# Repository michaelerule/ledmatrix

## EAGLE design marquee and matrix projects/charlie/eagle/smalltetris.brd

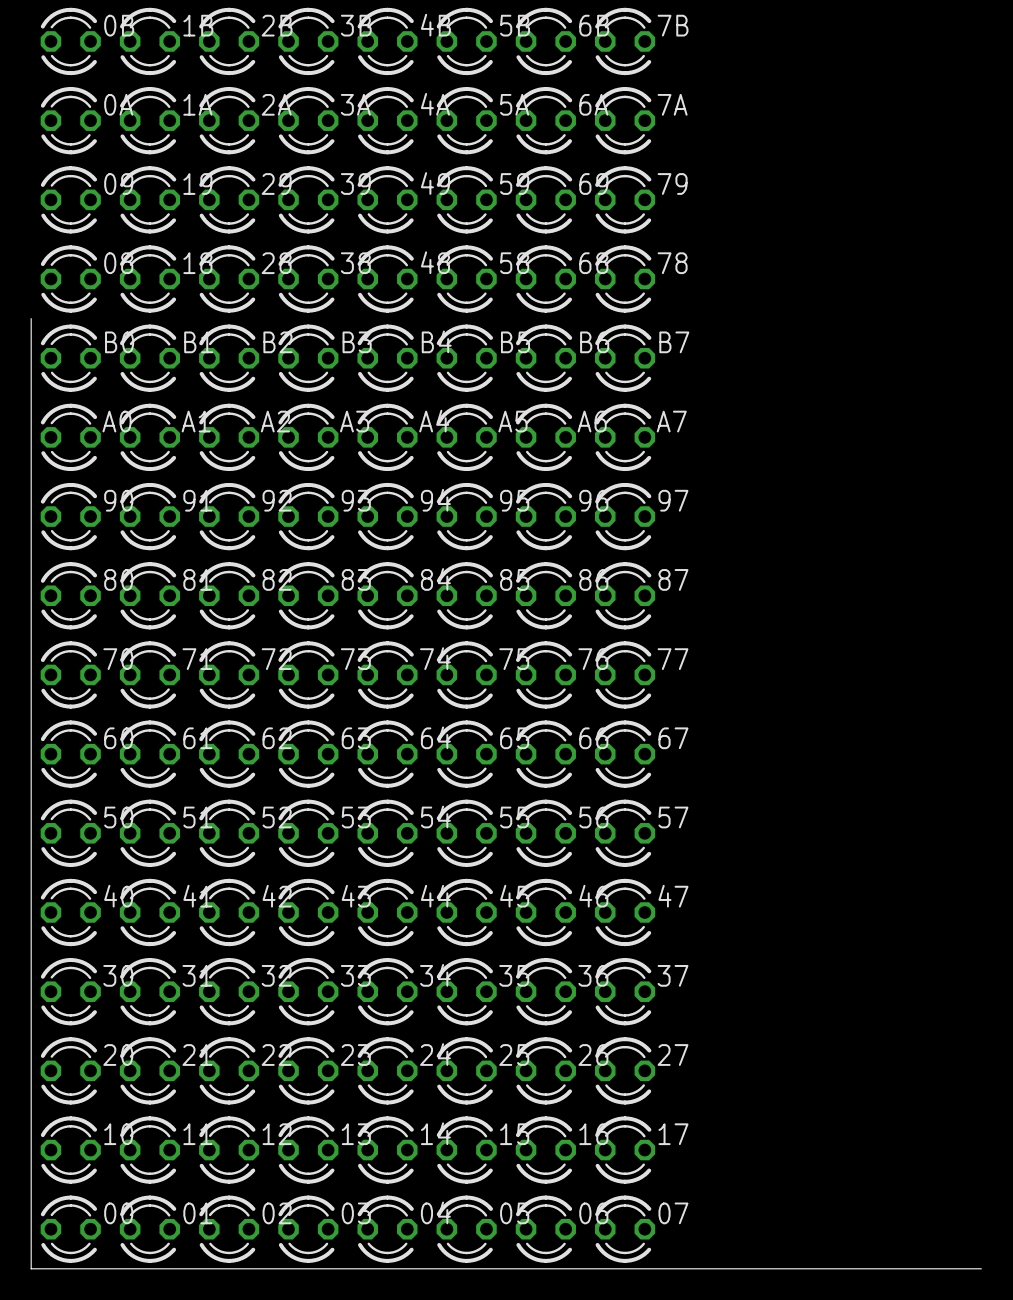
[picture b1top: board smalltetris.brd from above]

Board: 2 copper layers, 128 parts (0 on the bottom side), 13 nets, no tracks yet.

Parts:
00, 0A, 0B, 01, 1A, 1B, 02, 2A, 2B, 03, 3A, 3B, 04, 4A, 4B, 05, 5A, 5B, 06, 6A, 6B, 07, 7A, 7B, 08, 09, 10, 11, 12, 13, 14, 15, 16, 17, 18, 19, 20, 21, 22, 23, 24, 25, 26, 27, 28, 29, 30, 31, 32, 33, 34, 35, 36, 37, 38, 39, 40, 41, 42, 43, 44, 45, 46, 47, 48, 49, 50, 51, 52, 53, 54, 55, 56, 57, 58, 59, 60, 61, 62, 63, 64, 65, 66, 67, 68, 69, 70, 71, 72, 73, 74, 75, 76, 77, 78, 79, 80, 81, 82, 83, 84, 85, 86, 87, 90, 91, 92, 93, 94, 95, 96, 97: LED3MM
A0, A1, A2, A3, A4, A5, A6, A7: LED3MM
B0, B1, B2, B3, B4, B5, B6, B7: LED3MM

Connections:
D: 00.A, 11.A, 22.A, 33.A, 44.A, 55.A, 66.A, 77.A
S0: 00.K, 0A.A, 0B.A, 01.A, 02.A, 03.A, 04.A, 05.A, 06.A, 07.A, 08.A, 09.A, 10.K, 20.K, 30.K, 40.K, 50.K, 60.K, 70.K, 80.K, 90.K, A0.K, B0.K
S1: 01.K, 1A.A, 1B.A, 10.A, 11.K, 12.A, 13.A, 14.A, 15.A, 16.A, 17.A, 18.A, 19.A, 21.K, 31.K, 41.K, 51.K, 61.K, 71.K, 81.K, 91.K, A1.K, B1.K
S2: 02.K, 2A.A, 2B.A, 12.K, 20.A, 21.A, 22.K, 23.A, 24.A, 25.A, 26.A, 27.A, 28.A, 29.A, 32.K, 42.K, 52.K, 62.K, 72.K, 82.K, 92.K, A2.K, B2.K
S3: 03.K, 3A.A, 3B.A, 13.K, 23.K, 30.A, 31.A, 32.A, 33.K, 34.A, 35.A, 36.A, 37.A, 38.A, 39.A, 43.K, 53.K, 63.K, 73.K, 83.K, 93.K, A3.K, B3.K
S4: 04.K, 4A.A, 4B.A, 14.K, 24.K, 34.K, 40.A, 41.A, 42.A, 43.A, 44.K, 45.A, 46.A, 47.A, 48.A, 49.A, 54.K, 64.K, 74.K, 84.K, 94.K, A4.K, B4.K
S5: 05.K, 5A.A, 5B.A, 15.K, 25.K, 35.K, 45.K, 50.A, 51.A, 52.A, 53.A, 54.A, 55.K, 56.A, 57.A, 58.A, 59.A, 65.K, 75.K, 85.K, 95.K, A5.K, B5.K
S6: 06.K, 6A.A, 6B.A, 16.K, 26.K, 36.K, 46.K, 56.K, 60.A, 61.A, 62.A, 63.A, 64.A, 65.A, 66.K, 67.A, 68.A, 69.A, 76.K, 86.K, 96.K, A6.K, B6.K
S7: 07.K, 7A.A, 7B.A, 17.K, 27.K, 37.K, 47.K, 57.K, 67.K, 70.A, 71.A, 72.A, 73.A, 74.A, 75.A, 76.A, 77.K, 78.A, 79.A, 87.K, 97.K, A7.K, B7.K
S8: 08.K, 18.K, 28.K, 38.K, 48.K, 58.K, 68.K, 78.K, 80.A, 81.A, 82.A, 83.A, 84.A, 85.A, 86.A, 87.A
S9: 09.K, 19.K, 29.K, 39.K, 49.K, 59.K, 69.K, 79.K, 90.A, 91.A, 92.A, 93.A, 94.A, 95.A, 96.A, 97.A
S10: 0A.K, 1A.K, 2A.K, 3A.K, 4A.K, 5A.K, 6A.K, 7A.K, A0.A, A1.A, A2.A, A3.A, A4.A, A5.A, A6.A, A7.A
S11: 0B.K, 1B.K, 2B.K, 3B.K, 4B.K, 5B.K, 6B.K, 7B.K, B0.A, B1.A, B2.A, B3.A, B4.A, B5.A, B6.A, B7.A

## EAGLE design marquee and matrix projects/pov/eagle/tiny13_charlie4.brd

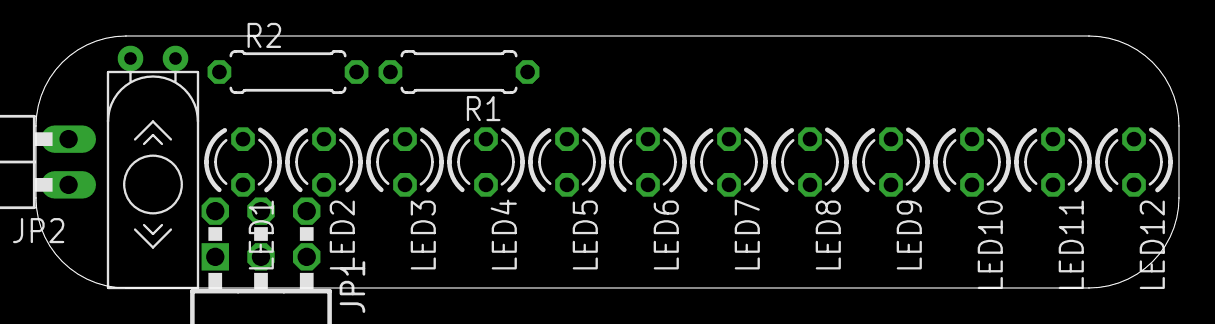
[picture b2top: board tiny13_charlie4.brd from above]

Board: 2 copper layers, 63.5 x 14.0 mm, 18 parts (1 on the bottom side), 8 nets, no tracks yet.

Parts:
IC1: TINY13-20SSU; 8S1
JP1: AVR-ISP-6R
JP2: 1X02/90
LED1, LED2, LED3, LED4, LED5, LED6, LED7, LED8, LED9, LED10, LED11, LED12: LED3MM
R1, R2: 0207/7
U$1: TILT_SWITCH_MECHANICAL

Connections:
GND: IC1.1, IC1.4, JP1.5, JP1.6, JP2.2, R1.2, R2.1
unnamed: IC1.2, LED3.K, LED4.A, LED5.K, LED6.A, LED7.A, LED8.K
unnamed: IC1.7, JP1.3, LED1.K, LED2.A, LED3.A, LED4.K, LED11.A, LED12.K
unnamed: R2.2, U$1.P$2
unnamed: IC1.3, LED7.K, LED8.A, LED9.K, LED10.A, LED11.K, LED12.A
unnamed: IC1.5, JP1.4, U$1.P$1
unnamed: IC1.6, JP1.1, LED1.A, LED2.K, LED5.A, LED6.K, LED9.A, LED10.K
VCC: IC1.8, JP1.2, JP2.1, R1.1

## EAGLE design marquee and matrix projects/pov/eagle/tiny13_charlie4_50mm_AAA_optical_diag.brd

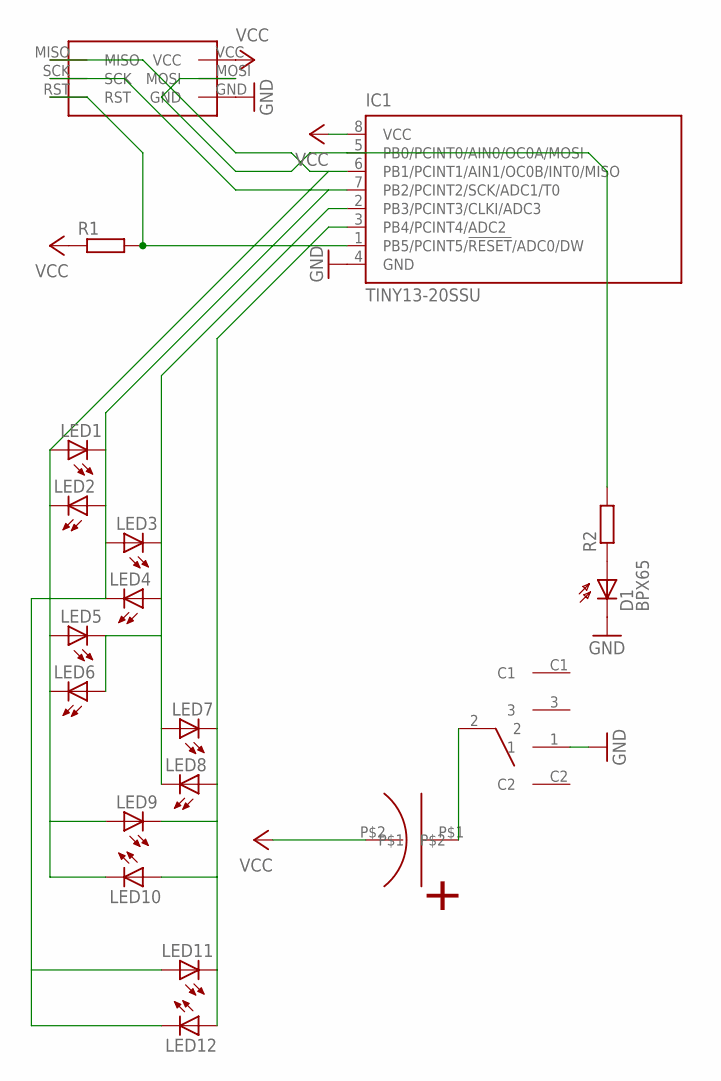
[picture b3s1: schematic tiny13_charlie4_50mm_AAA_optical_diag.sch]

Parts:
D1: BPX65
IC1: TINY13-20SSU; 8S1
LED1, LED2, LED3, LED4, LED5, LED6, LED7, LED8, LED9, LED10, LED11, LED12: LED3MM
R1, R2: R-EU_0204/5; 0204/5
U$2: AVR_ISP_6_PIN_1X6_SMT_CONTACT_BIG; CONTACT_ISP_PROGRAMMER_1X6_ATMEL
U$4: SWITCH
U$5: NICHICON_12F; NICHICON_10X30

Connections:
GND: D1.K (C), IC1.4 (GND), U$2.GND, U$4.1
unnamed: IC1.2 (PB3/PCINT3/CLKI/ADC3), LED3.K (C), LED4.A, LED5.K (C), LED6.A, LED7.A, LED8.K (C)
unnamed: IC1.7 (PB2/PCINT2/SCK/ADC1/T0), LED1.K (C), LED2.A, LED3.A, LED4.K (C), LED11.A, LED12.K (C), U$2.SCK
unnamed: D1.A, R2.1
unnamed: IC1.3 (PB4/PCINT4/ADC2), LED7.K (C), LED8.A, LED9.K (C), LED10.A, LED11.K (C), LED12.A
unnamed: IC1.5 (PB0/PCINT0/AIN0/OC0A/MOSI), R2.2, U$2.MOSI
unnamed: IC1.1 (PB5/PCINT5/!RESET!/ADC0/DW), R1.2, U$2.RST
unnamed: U$4.2, U$5.P$1
unnamed: IC1.6 (PB1/PCINT1/AIN1/OC0B/INT0/MISO), LED1.A, LED2.K (C), LED5.A, LED6.K (C), LED9.A, LED10.K (C), U$2.MISO
VCC: IC1.8 (VCC), R1.1, U$2.VCC, U$5.P$2

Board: 2 copper layers, 19 parts (2 on the bottom side), 10 nets, no tracks yet.

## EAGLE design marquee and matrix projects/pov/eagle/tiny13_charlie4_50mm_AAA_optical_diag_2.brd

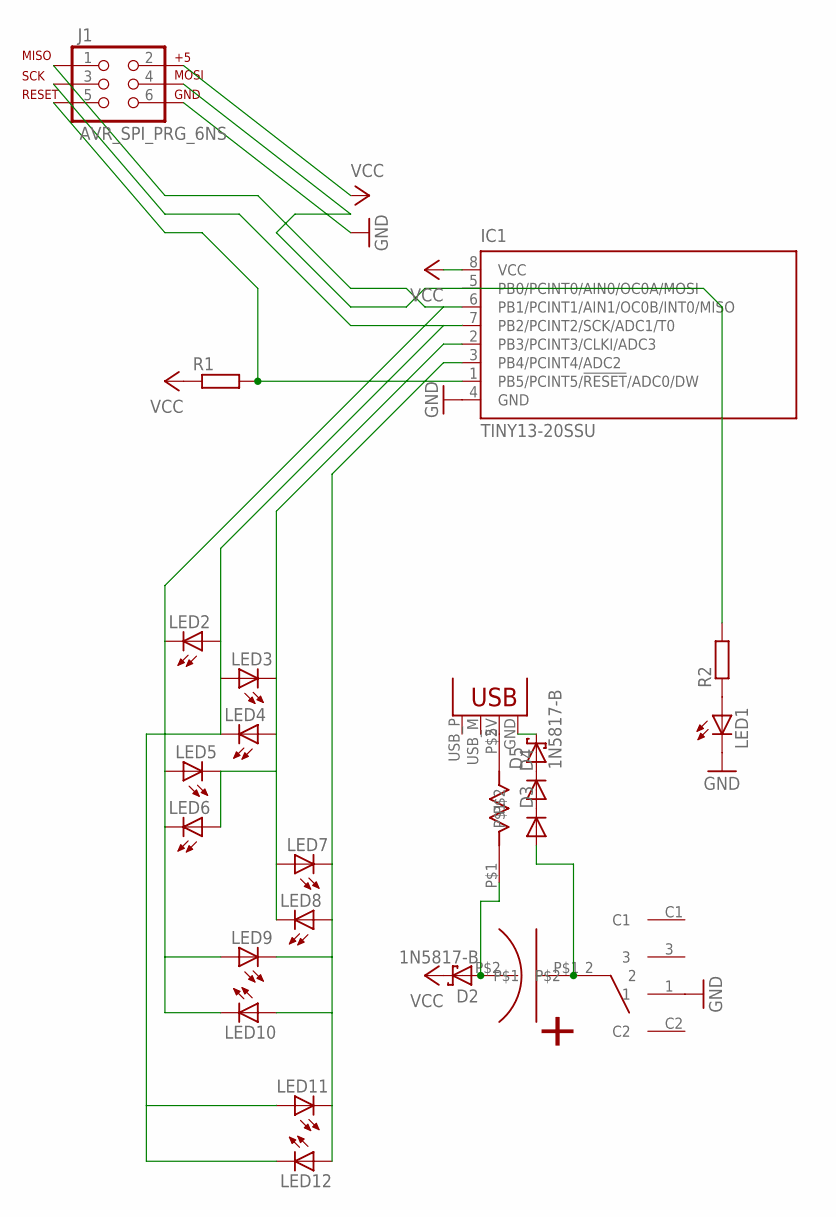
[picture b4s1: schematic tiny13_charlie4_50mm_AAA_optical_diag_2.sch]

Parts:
D2, D5: 1N5817-B; DO41-7.6
D3, D4: DIODE-D-5; D-5
IC1: TINY13-20SSU; 8S1
J1: AVR_SPI_PRG_6NS; 2X3-NS
LED1, LED2, LED3, LED4, LED5, LED6, LED7, LED8, LED9, LED10, LED11, LED12: LED3MM
R1, R2: R-EU_0204/5; 0204/5
U$1: R-7
U$4: SWITCH
U$5: NICHICON_12F; NICHICON_10X30
X1: USBPCB; USB-A-PCB

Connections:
GND: IC1.4 (GND), J1.6, LED1.K (C), U$4.1
unnamed: IC1.2 (PB3/PCINT3/CLKI/ADC3), LED3.K (C), LED4.A, LED5.K (C), LED6.A, LED7.A, LED8.K (C)
unnamed: IC1.7 (PB2/PCINT2/SCK/ADC1/T0), J1.3, LED2.A, LED3.A, LED4.K (C), LED11.A, LED12.K (C)
unnamed: LED1.A, R2.1
unnamed: IC1.3 (PB4/PCINT4/ADC2), LED7.K (C), LED8.A, LED9.K (C), LED10.A, LED11.K (C), LED12.A
unnamed: IC1.5 (PB0/PCINT0/AIN0/OC0A/MOSI), J1.4, R2.2
unnamed: IC1.1 (PB5/PCINT5/!RESET!/ADC0/DW), J1.5, R1.2
unnamed: D3.A, U$4.2, U$5.P$1
unnamed: IC1.6 (PB1/PCINT1/AIN1/OC0B/INT0/MISO), J1.1, LED2.K (C), LED5.A, LED6.K (C), LED9.A, LED10.K (C)
unnamed: D3.C, D4.A
unnamed: D4.C, D5.A
unnamed: D5.C, X1.GND
unnamed: U$1.P$2, X1.5V (VBUS)
unnamed: D2.A, U$1.P$1, U$5.P$2
VCC: D2.C, IC1.8 (VCC), R1.1

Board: 2 copper layers, 24 parts (3 on the bottom side), 15 nets, no tracks yet.

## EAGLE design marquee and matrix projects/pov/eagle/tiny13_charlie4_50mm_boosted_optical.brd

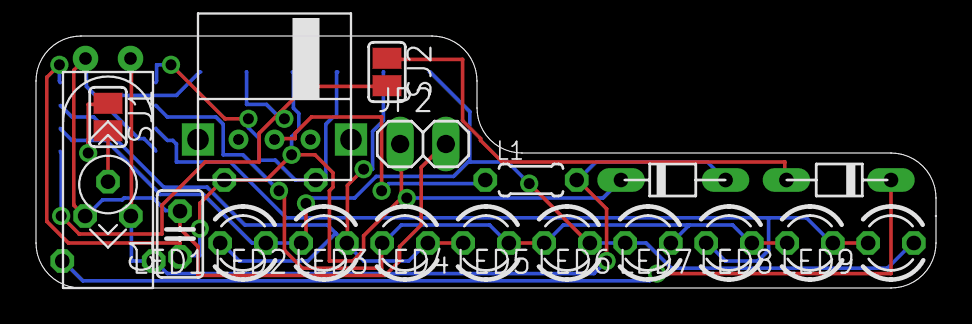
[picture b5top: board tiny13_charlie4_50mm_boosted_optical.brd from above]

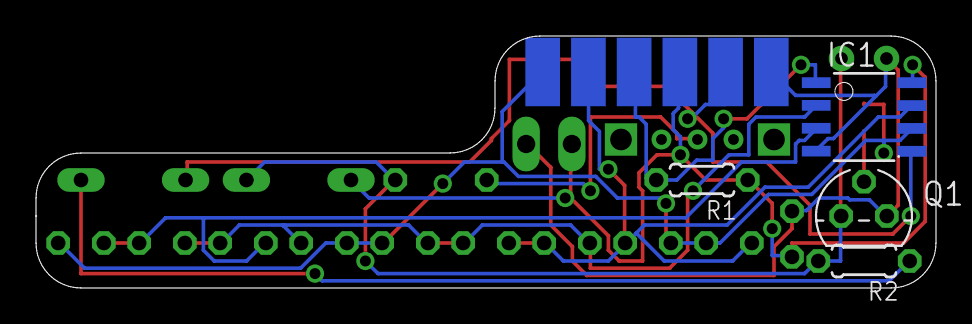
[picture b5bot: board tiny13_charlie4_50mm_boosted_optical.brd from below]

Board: 2 copper layers, 50.0 x 14.0 mm, 23 parts (5 on the bottom side), 13 nets.

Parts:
C1: C025-025X050
IC1: TINY13-20SSU; 8S1
JP2: 1X02
L1: 0204/5
LED1, LED2, LED3, LED4, LED5, LED6, LED7, LED8, LED9: LED3MM
Q1: BSS101; TO92
R1, R2: 0204/5
SJ1, SJ2: SJ
U$1: TILT_SWITCH_MECHANICAL
U$2: AVR_ISP_6_PIN_1X6_SMT_CONTACT_PROGRAMMER; CONTACT_ISP_PROGRAMMER_1X6_ATMEL
U$3, U$4: D-6; D-7.5
U$5: SWITCH

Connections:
GND: C1.2, IC1.4, JP2.2, Q1.1, U$1.P$1, U$2.GND
unnamed: IC1.2, LED3.K, LED4.A, LED5.K, LED6.A, LED7.A, LED8.K
unnamed: IC1.7, LED1.K, LED2.A, LED3.A, LED4.K, U$2.SCK
unnamed: L1.2, Q1.3, R2.2, U$1.P$2, U$3.A
unnamed: IC1.3, LED7.K, LED8.A, LED9.K
unnamed: R2.1, U$4.C
unnamed: IC1.1, R1.2, U$2.RST
unnamed: IC1.5, SJ2.2, U$2.MOSI
unnamed: IC1.6, LED1.A, LED2.K, LED5.A, LED6.K, LED9.A, SJ1.1, U$2.MISO
unnamed: Q1.2, SJ1.2
unnamed: SJ2.1, U$4.A
unnamed: L1.1, U$5.2
VCC: C1.1, IC1.8, JP2.1, R1.1, U$2.VCC, U$3.C

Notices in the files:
parts and their libraries:
SparkFun: Licensing: CC v3.0 Share-Alike You are welcome to use this library for commercial purposes.
